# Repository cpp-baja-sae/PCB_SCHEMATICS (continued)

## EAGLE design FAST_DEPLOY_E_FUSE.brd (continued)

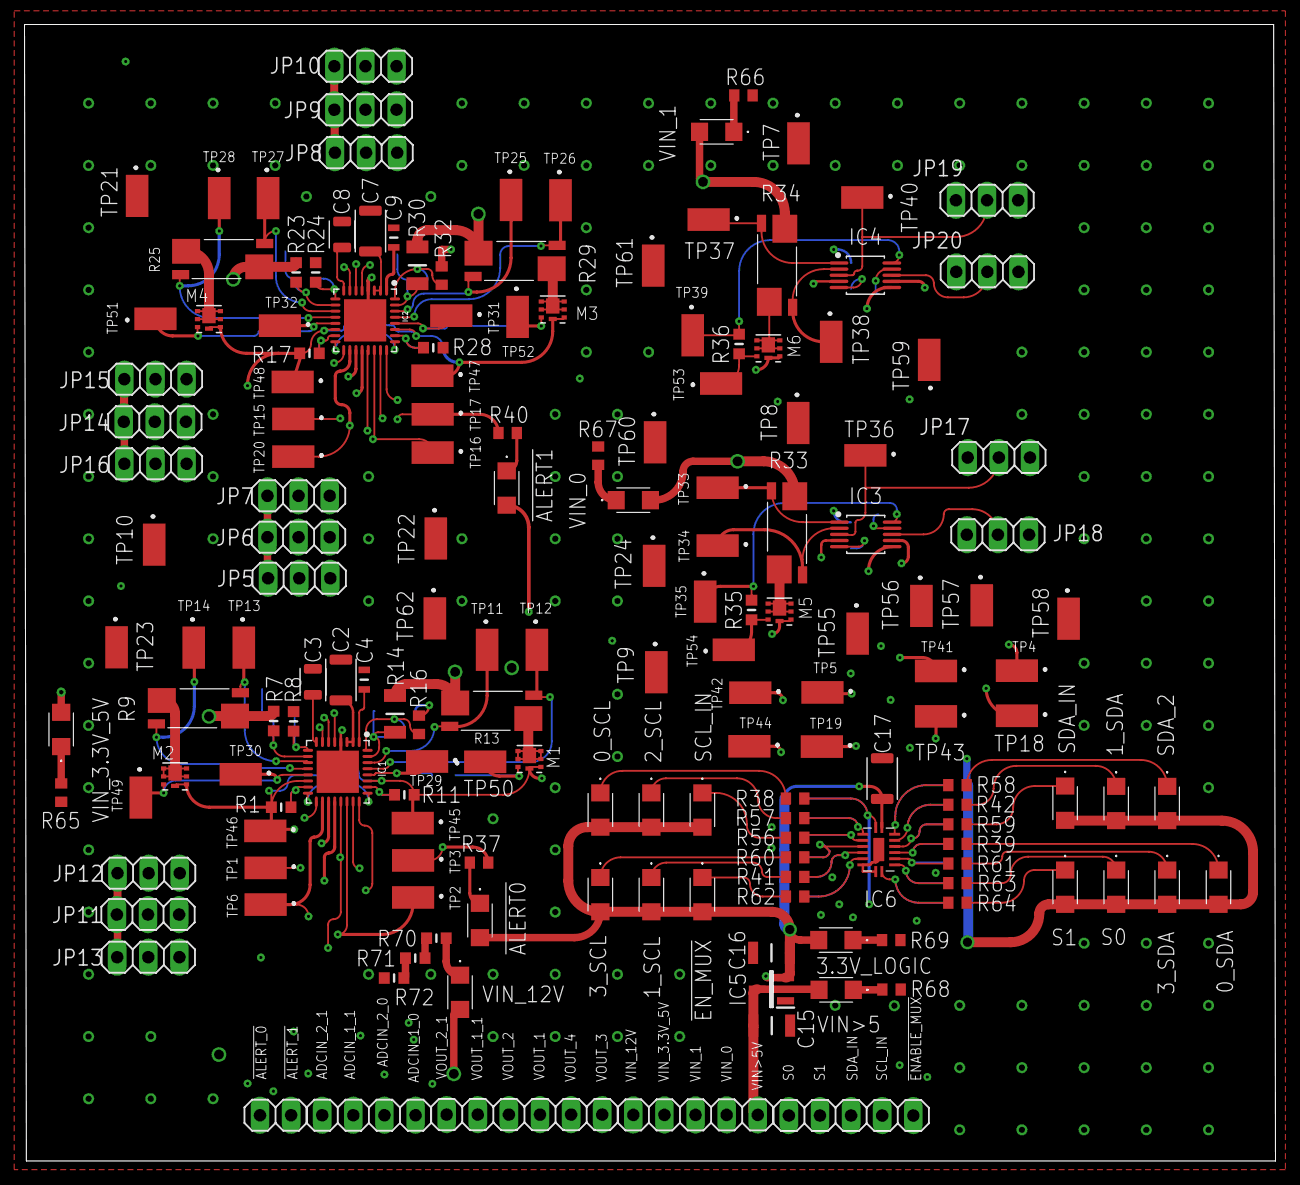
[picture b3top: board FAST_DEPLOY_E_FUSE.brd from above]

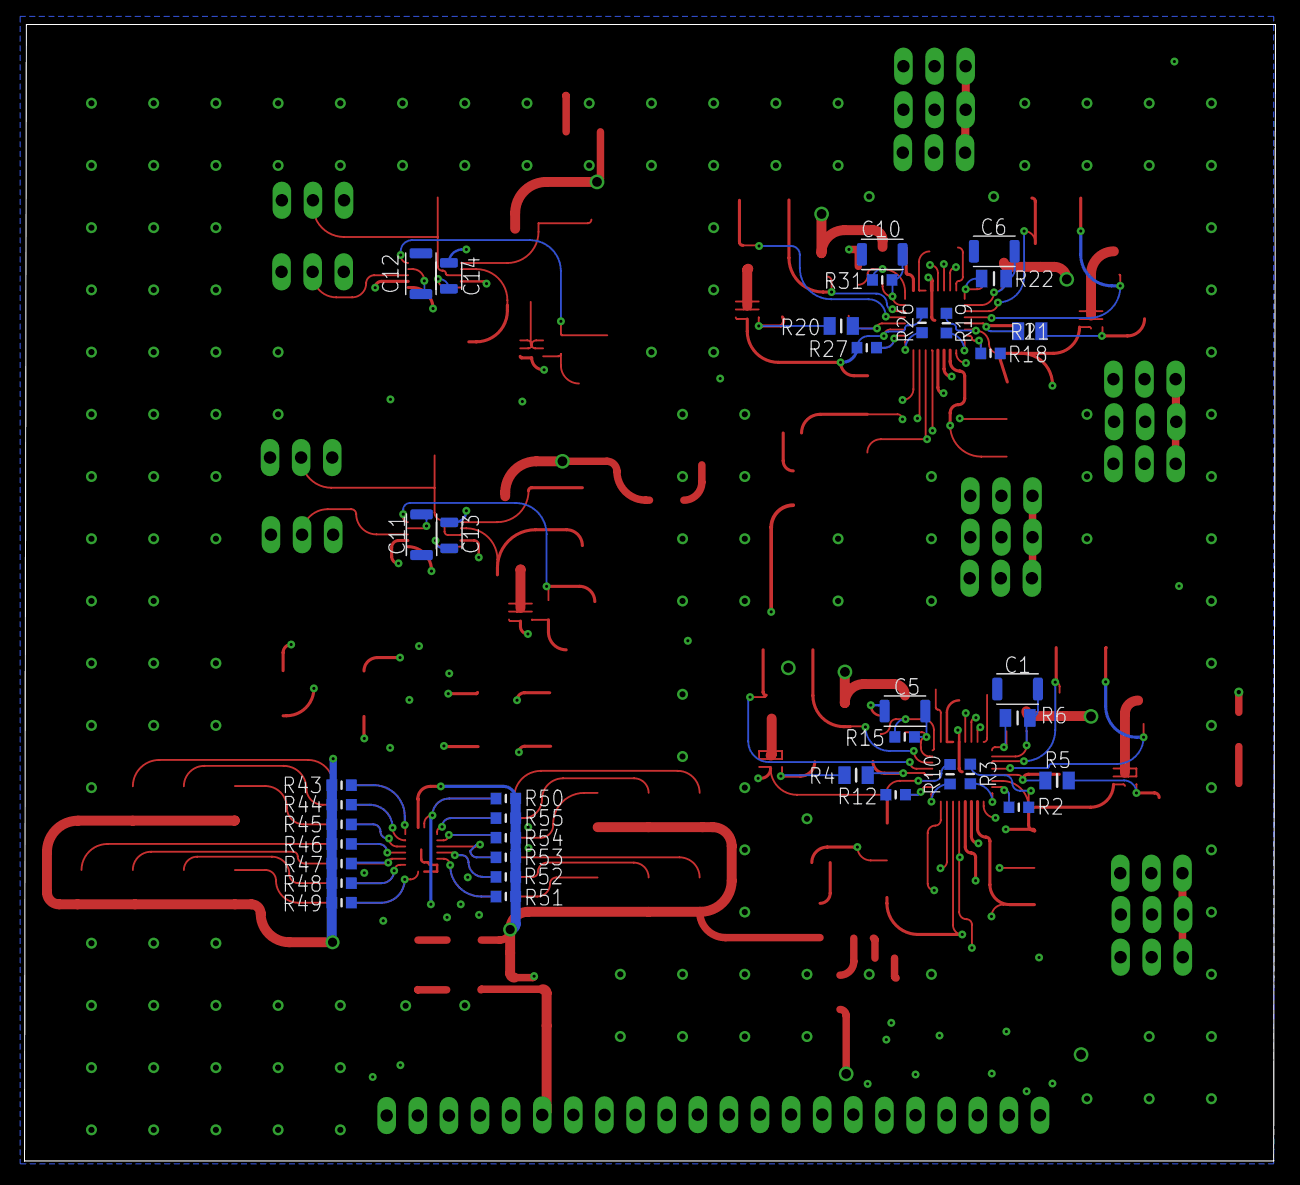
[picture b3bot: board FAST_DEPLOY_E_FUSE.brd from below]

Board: 4 copper layers, 102.1 x 92.8 mm, 205 parts (37 on the bottom side), 127 nets.

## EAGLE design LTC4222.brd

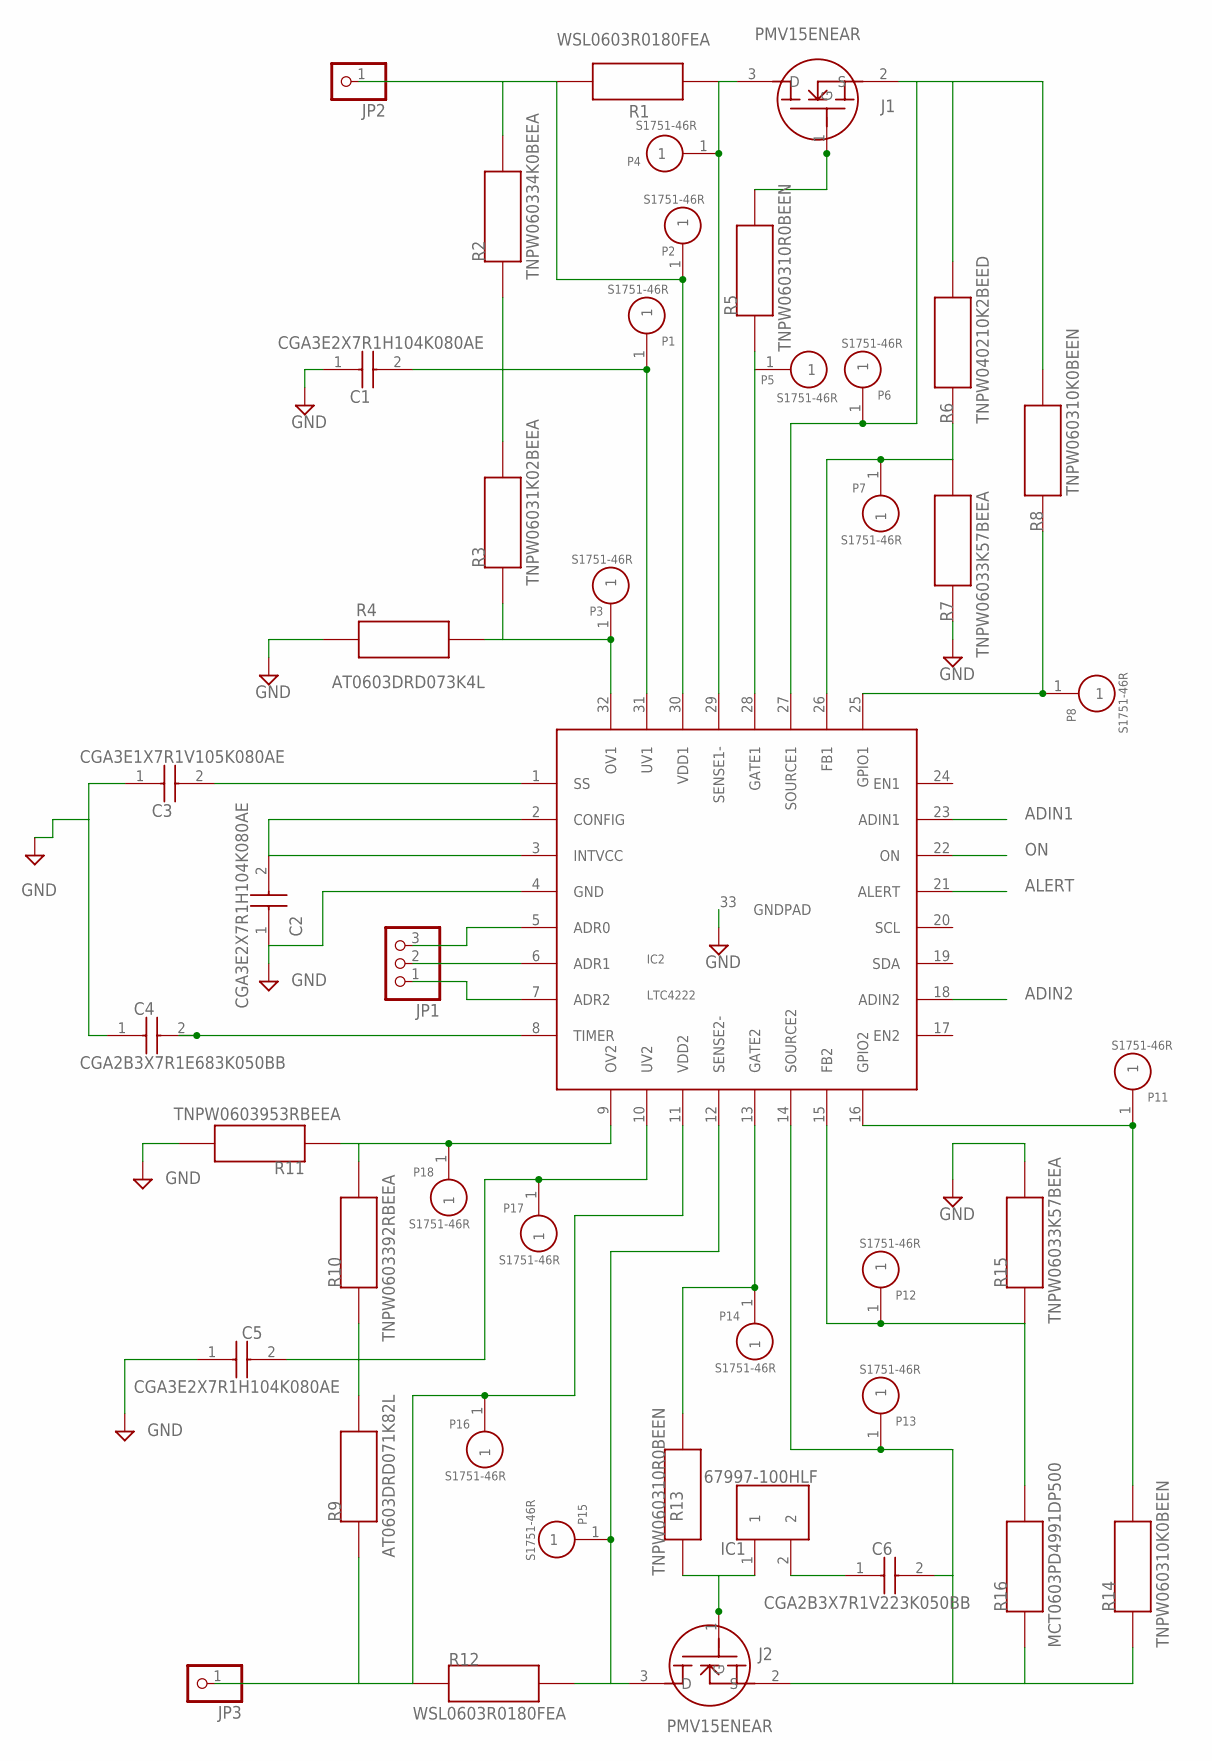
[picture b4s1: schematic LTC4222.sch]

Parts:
C1, C2, C5: CGA3E2X7R1H104K080AE; CAPC1608X80M
C3: CGA3E1X7R1V105K080AE; CAPC1608X80M
C4: CGA2B3X7R1E683K050BB; CAPC1005X50M
C6: CGA2B3X7R1V223K050BB; CAPC1005X50M
IC1: 67997-100HLF; HDRV2W64P254_2X1_241X508X838B
IC2: LTC4222; QFN50P500X500X75-33T345M
J1, J2: PMV15ENEAR; SOT95P230X110-3M
JP1: PINHD-1X3; 1X03
JP2, JP3: PINHD-1X1; 1X01
P1, P2, P3, P4, P5, P6, P7, P8, P11, P12, P13, P14, P15, P16, P17, P18: S1751-46R
R1, R12: WSL0603R0180FEA; RESC1507X40M
R2: TNPW060334K0BEEA; AT0603
R3: TNPW06031K02BEEA; AT0603
R4: AT0603DRD073K4L; RESC1608X45M
R5, R13: TNPW060310R0BEEN; AT0603
R6: TNPW040210K2BEED; RESC1005X35M
R7, R15: TNPW06033K57BEEA; AT0603
R8, R14: TNPW060310K0BEEN; AT0603
R9: AT0603DRD071K82L; RESC1608X45M
R10: TNPW0603392RBEEA; AT0603
R11: TNPW0603953RBEEA; AT0603
R16: MCT0603PD4991DP500; RESC1508X47M

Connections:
ADIN1: IC2.23 (ADIN1); also elsewhere on the board
ADIN2: IC2.18 (ADIN2); also elsewhere on the board
ALERT: IC2.21 (ALERT); also elsewhere on the board
GND: C1.1, C2.1, C3.1, C4.1, C5.1, IC2.4 (GND), R4.2, R7.1, R11.2, R15.2
unnamed: J1.1 (G), R5.2
unnamed: IC2.30 (VDD1), JP2.1, P2.1, R1.1, R2.2
unnamed 6: IC2.24 (EN1); also elsewhere on the board
unnamed 7: IC2.20 (SCL); also elsewhere on the board
unnamed 8: IC2.19 (SDA); also elsewhere on the board
unnamed: IC2.29 (SENSE1-), J1.3 (D), P4.1, R1.2
unnamed: IC2.32 (OV1), P3.1, R3.1, R4.1
unnamed: C1.2, IC2.31 (UV1), P1.1, R2.1, R3.2
unnamed 12: IC2.17 (EN2); also elsewhere on the board
unnamed: C2.2, IC2.2 (CONFIG), IC2.3 (INTVCC)
unnamed: IC2.28 (GATE1), P5.1, R5.1
unnamed: IC2.27 (SOURCE1), J1.2 (S), P6.1, R6.2, R8.2
unnamed: IC2.7 (ADR2), JP1.1
unnamed: IC2.25 (GPIO1), P8.1, R8.1
unnamed: C4.2, IC2.8 (TIMER)
unnamed: C3.2, IC2.1 (SS)
unnamed: IC2.13 (GATE2), P14.1, R13.2
unnamed: IC2.9 (OV2), P18.1, R10.2, R11.1
unnamed: IC2.12 (SENSE2-), J2.3 (D), P15.1, R12.2
unnamed: IC2.11 (VDD2), JP3.1, P16.1, R9.1, R12.1
unnamed: IC1.1, J2.1 (G), R13.1
unnamed: C6.2, IC2.14 (SOURCE2), J2.2 (S), P13.1, R14.1, R16.1
unnamed: C6.1, IC1.2
unnamed: IC2.15 (FB2), P12.1, R15.1, R16.2
unnamed: IC2.16 (GPIO2), P11.1, R14.2
unnamed: C5.2, IC2.10 (UV2), P17.1, R9.2, R10.1
unnamed: IC2.26 (FB1), P7.1, R6.1, R7.2
unnamed: IC2.6 (ADR1), JP1.2
unnamed: IC2.5 (ADR0), JP1.3
ON: IC2.22 (ON); also elsewhere on the board

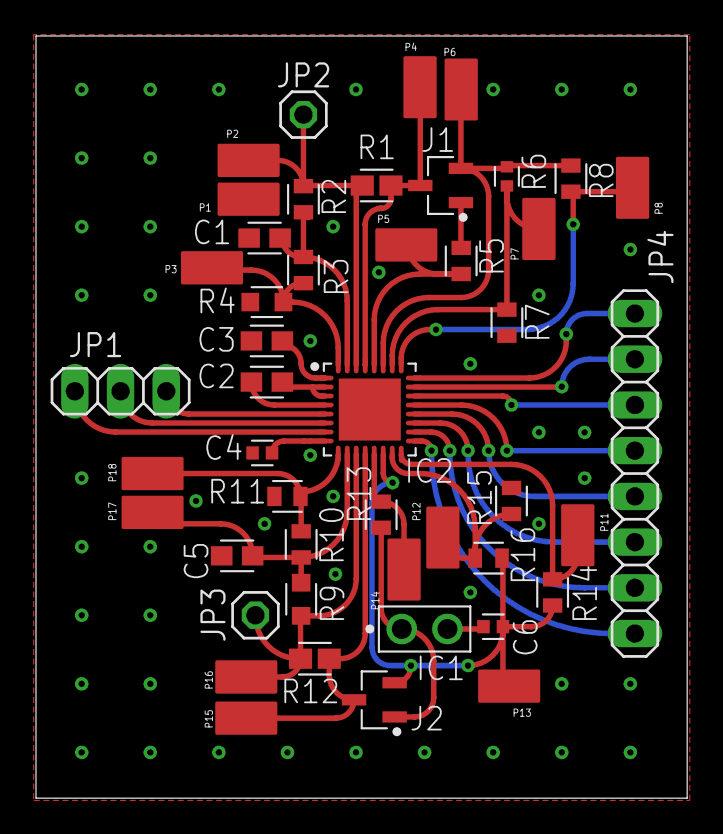
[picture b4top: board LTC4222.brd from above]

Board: 2 copper layers, 36.2 x 42.3 mm, 46 parts (0 on the bottom side), 34 nets.

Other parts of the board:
JP4: 1X08

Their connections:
ADIN1: JP4.2; also elsewhere on the board
ADIN2: JP4.7; also elsewhere on the board
ALERT: JP4.4; also elsewhere on the board
unnamed 6: JP4.1; also elsewhere on the board
unnamed 7: JP4.5; also elsewhere on the board
unnamed 8: JP4.6; also elsewhere on the board
unnamed 12: JP4.8; also elsewhere on the board
ON: JP4.3; also elsewhere on the board
